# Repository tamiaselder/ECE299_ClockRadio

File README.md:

UVic ECE 299 term project repository, Clock radio

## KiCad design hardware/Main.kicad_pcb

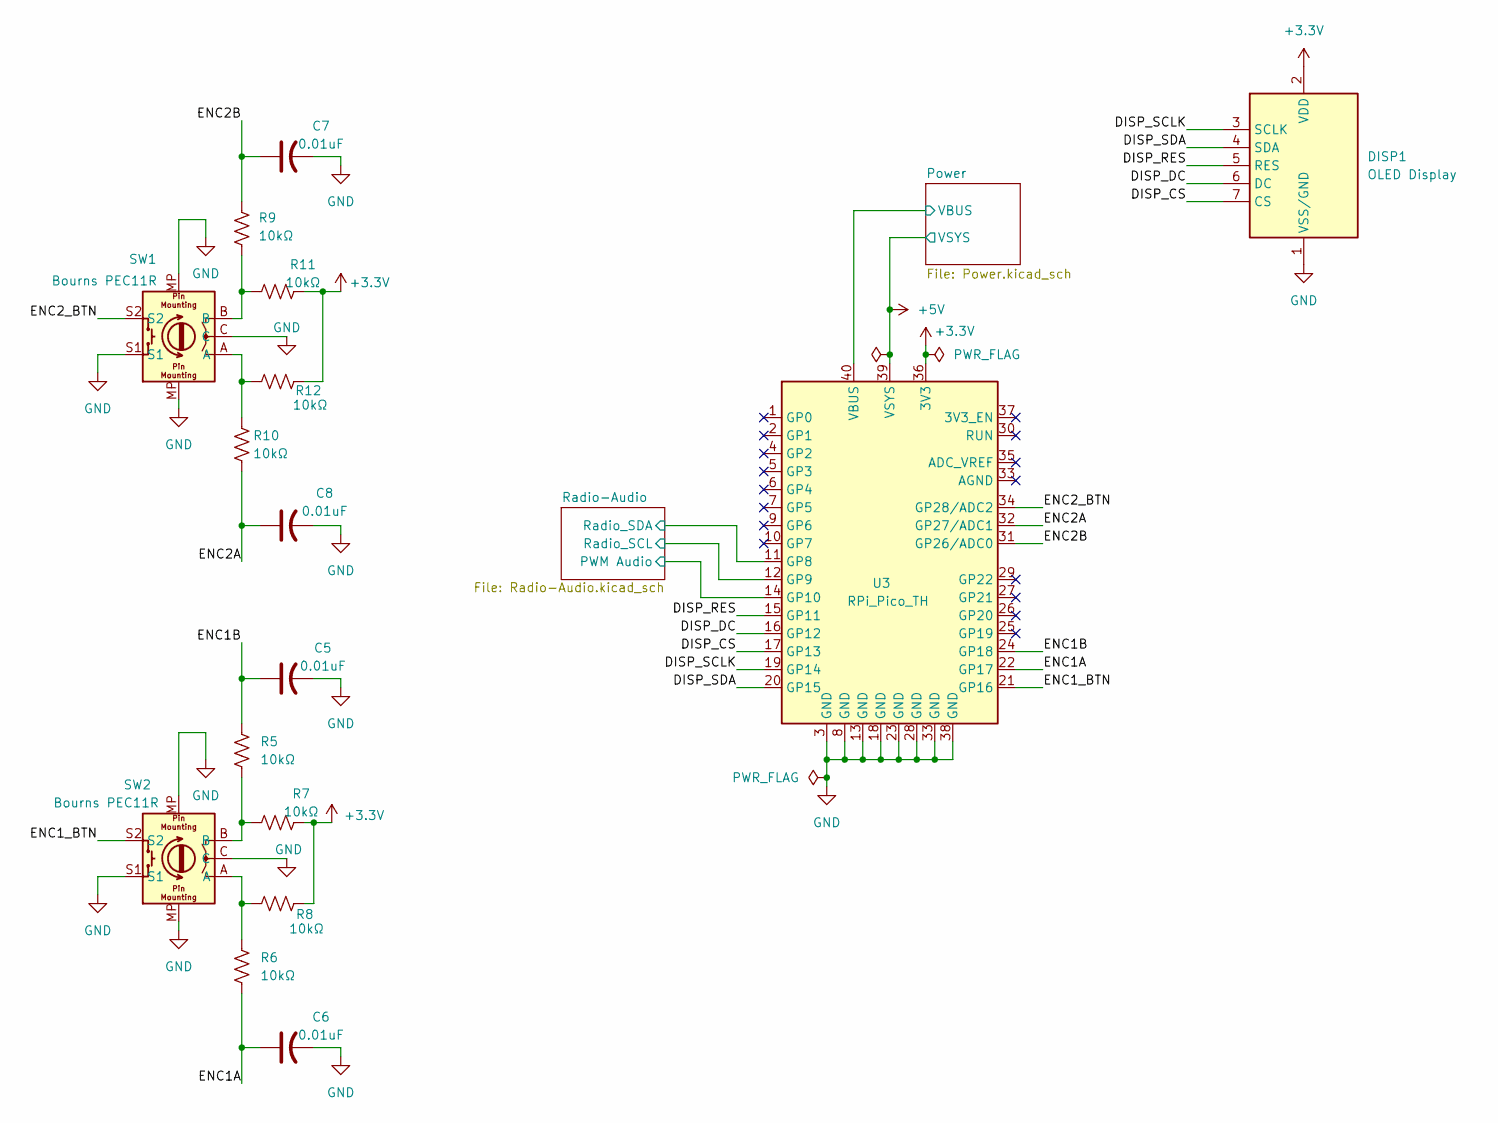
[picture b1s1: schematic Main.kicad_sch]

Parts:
C5, C6, C7, C8: 0.01uF; C_1206_3216Metric
DISP1: OLED Display; PinHeader_1x07_P2.00mm_Vertical
R5, R6, R7, R8, R9, R10, R11, R12: 10kΩ; R_1206_3216Metric
SW1, SW2: Bourns PEC11R; RotaryEncoder_Alps_EC12E-Switch_Vertical_H20mm
U3: RPi_Pico_TH

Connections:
+3.3V: DISP1.2 (VDD), R7.2, R8.2, R11.2, R12.2, U3.36 (3V3); also elsewhere on the board
+5V: U3.39 (VSYS); also elsewhere on the board
/DISP_CS: DISP1.7 (CS), U3.17 (GP13)
/DISP_DC: DISP1.6 (DC), U3.16 (GP12)
/DISP_RES: DISP1.5 (RES), U3.15 (GP11)
/DISP_SCLK: DISP1.3 (SCLK), U3.19 (GP14)
/DISP_SDA: DISP1.4 (SDA), U3.20 (GP15)
/ENC1A: C6.1, R6.1, U3.22 (GP17)
/ENC1B: C5.1, R5.2, U3.24 (GP18)
/ENC1_BTN: SW2.S2, U3.21 (GP16)
/ENC2A: C8.1, R10.1, U3.32 (GP27/ADC1)
/ENC2B: C7.1, R9.2, U3.31 (GP26/ADC0)
/ENC2_BTN: SW1.S2, U3.34 (GP28/ADC2)
/Power/VBUS: U3.40 (VBUS); also elsewhere on the board
/Radio-Audio/PWM Audio: U3.14 (GP10); also elsewhere on the board
/Radio-Audio/Radio_SCL: U3.12 (GP9); also elsewhere on the board
/Radio-Audio/Radio_SDA: U3.11 (GP8); also elsewhere on the board
GND: C5.2, C6.2, C7.2, C8.2, DISP1.1 (VSS/GND), SW1.C, SW1.MP, SW1.S1, SW2.C, SW2.MP, SW2.S1, U3.3 (GND), U3.8 (GND), U3.13 (GND), U3.18 (GND), U3.23 (GND), U3.28 (GND), U3.33 (GND), U3.38 (GND); also elsewhere on the board
unnamed: R5.1, R7.1, SW2.B
unnamed: R6.2, R8.1, SW2.A
unnamed: R10.2, R12.1, SW1.A
unnamed: R9.1, R11.1, SW1.B

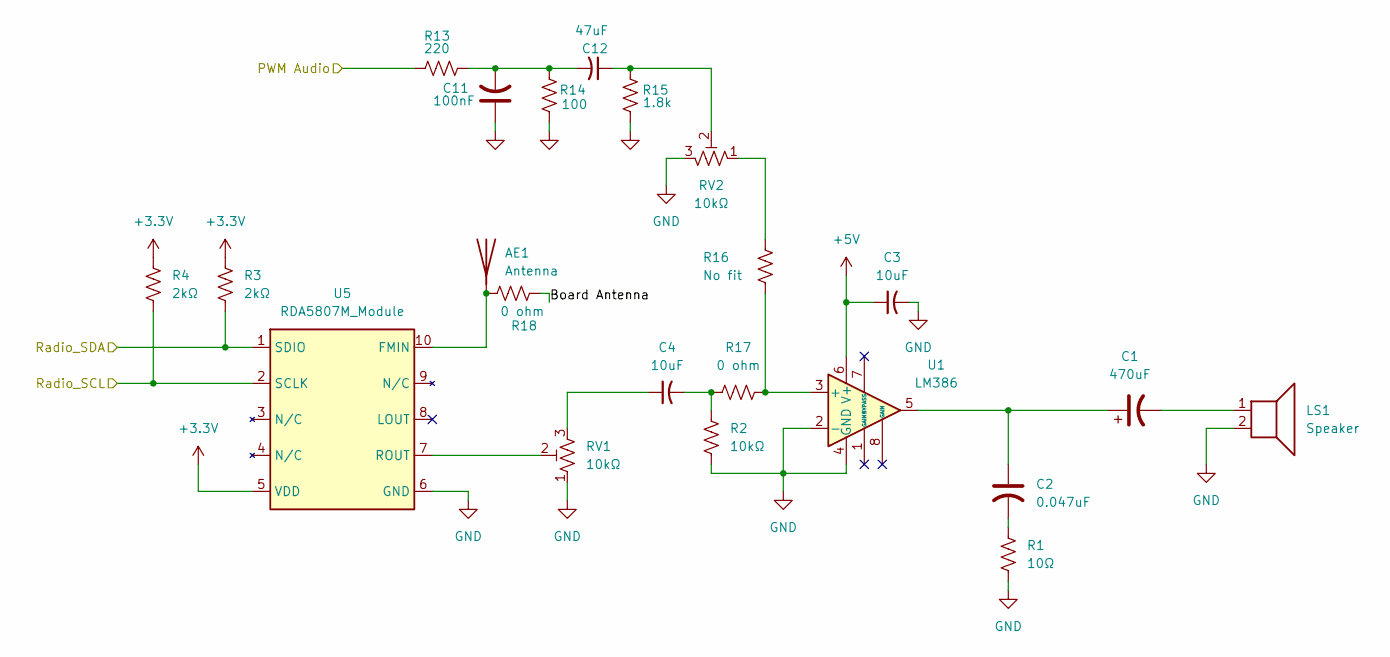
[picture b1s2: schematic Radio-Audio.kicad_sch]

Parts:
AE1: Antenna; PinHeader_1x01_P2.00mm_Vertical
C1: 470uF; CP_EIA-7343-30_AVX-N
C2: 0.047uF; C_1206_3216Metric
C3, C4: 10uF; C_1206_3216Metric
C11: 100nF; C_1206_3216Metric
C12: 47uF; C_1206_3216Metric
LS1: Speaker; TerminalBlock_MaiXu_MX126-5.0-02P_1x02_P5.00mm
R1: 10Ω; R_1206_3216Metric
R2: 10kΩ; R_1206_3216Metric
R3, R4: 2kΩ; R_1206_3216Metric
R13: 220; R_1206_3216Metric
R14: 100; R_1206_3216Metric
R15: 1.8k; R_1206_3216Metric
R16: No fit; R_1206_3216Metric
R17, R18: 0 ohm; R_1206_3216Metric
RV1, RV2: 10kΩ; Potentiometer_Bourns_3314J_Vertical
U1: LM386; DIP-8_W7.62mm_Socket
U5: RDA5807M_Module; RDA5807M_Module_SM

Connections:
+3.3V: R3.2, R4.1, U5.5 (VDD); also elsewhere on the board
+5V: C3.1, U1.6 (V+); also elsewhere on the board
/Radio-Audio/Board Antenna: R18.2
/Radio-Audio/PWM Audio: R13.2; also elsewhere on the board
/Radio-Audio/Radio_SCL: R4.2, U5.2 (SCLK); also elsewhere on the board
/Radio-Audio/Radio_SDA: R3.1, U5.1 (SDIO); also elsewhere on the board
GND: C3.2, C11.1, LS1.2, R1.2, R2.2, R14.1, R15.1, RV1.1, RV2.3, U1.2 (-), U1.4 (GND), U5.6 (GND); also elsewhere on the board
unnamed: AE1.1 (A), R18.1, U5.10 (FMIN)
unnamed: C1.1, C2.1, U1.5
unnamed: C1.2, LS1.1
unnamed: C2.2, R1.1
unnamed: C4.1, RV1.3
unnamed: C4.2, R2.1, R17.1
unnamed: C11.2, C12.2, R13.1, R14.2
unnamed: C12.1, R15.2, RV2.2
unnamed: R16.1, RV2.1
unnamed: R16.2, R17.2, U1.3 (+)
unnamed: RV1.2, U5.7 (ROUT)

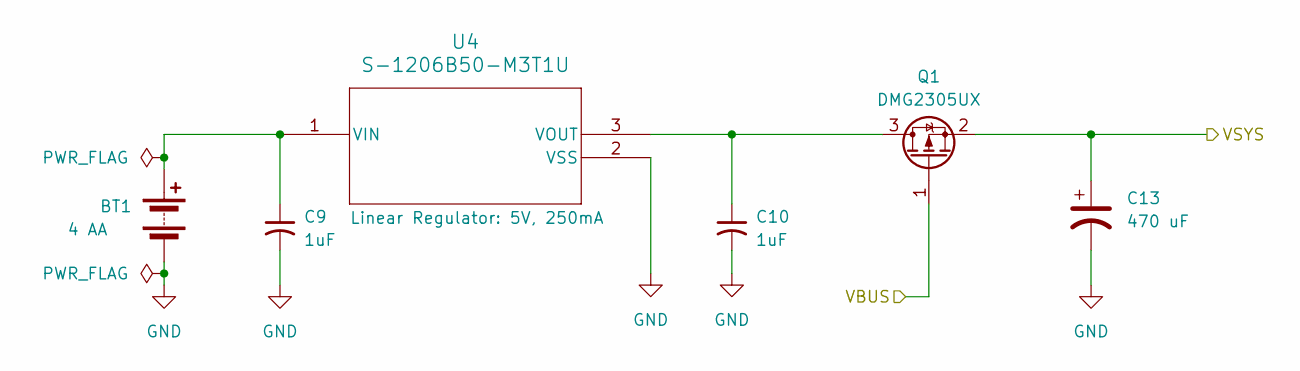
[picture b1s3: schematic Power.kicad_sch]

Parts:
BT1: 4 AA; TerminalBlock_MaiXu_MX126-5.0-02P_1x02_P5.00mm
C9, C10: 1uF; C_1206_3216Metric
C13: 470 uF; CP_EIA-7343-30_AVX-N
Q1: DMG2305UX; SOT-23
U4: S-1206B50-M3T1U; SOT-23-3

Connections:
+5V: C13.1, Q1.2 (S); also elsewhere on the board
/Power/VBUS: Q1.1 (G); also elsewhere on the board
GND: BT1.2 (-), C9.2, C10.2, C13.2, U4.2 (VSS); also elsewhere on the board
unnamed: BT1.1 (+), C9.1, U4.1 (VIN)
unnamed: C10.1, Q1.3 (D), U4.3 (VOUT)

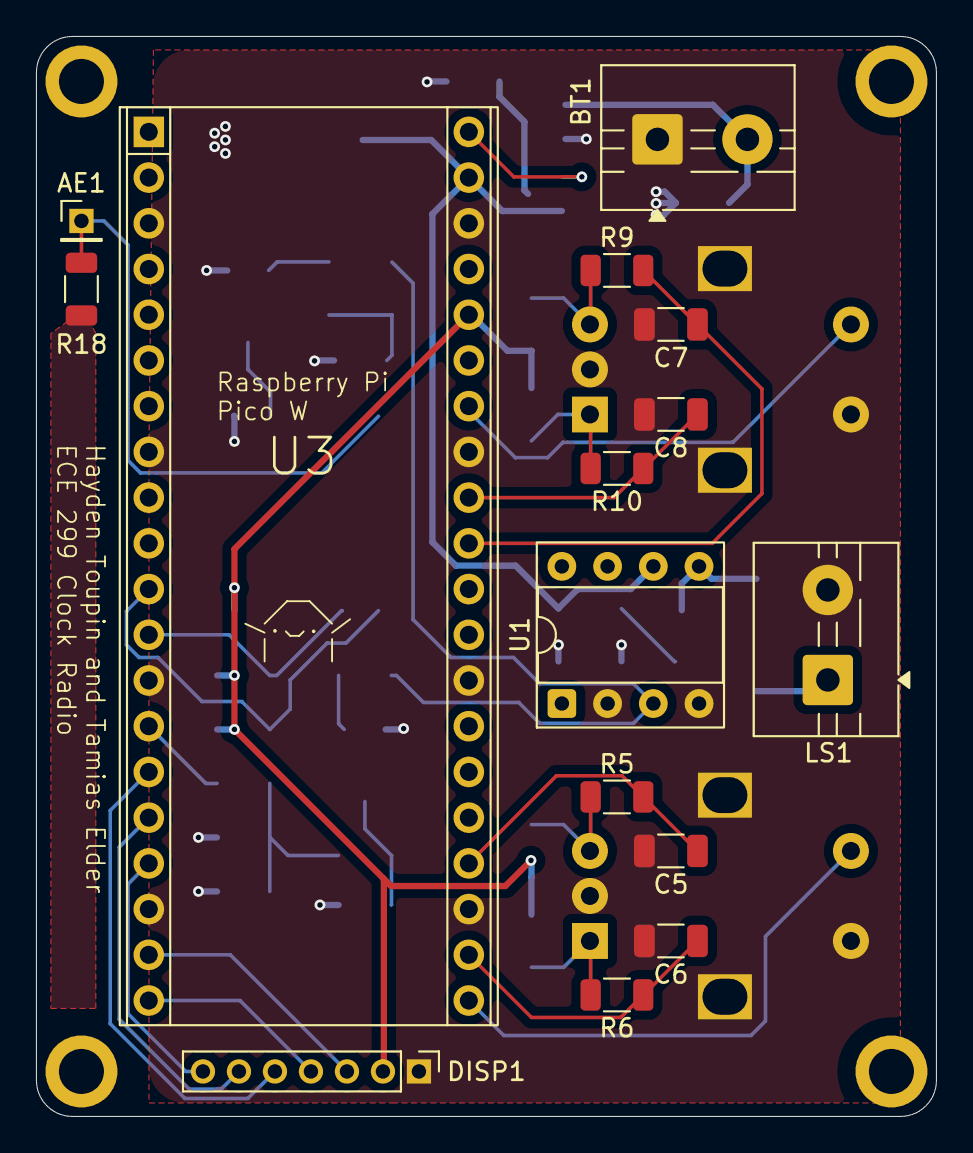
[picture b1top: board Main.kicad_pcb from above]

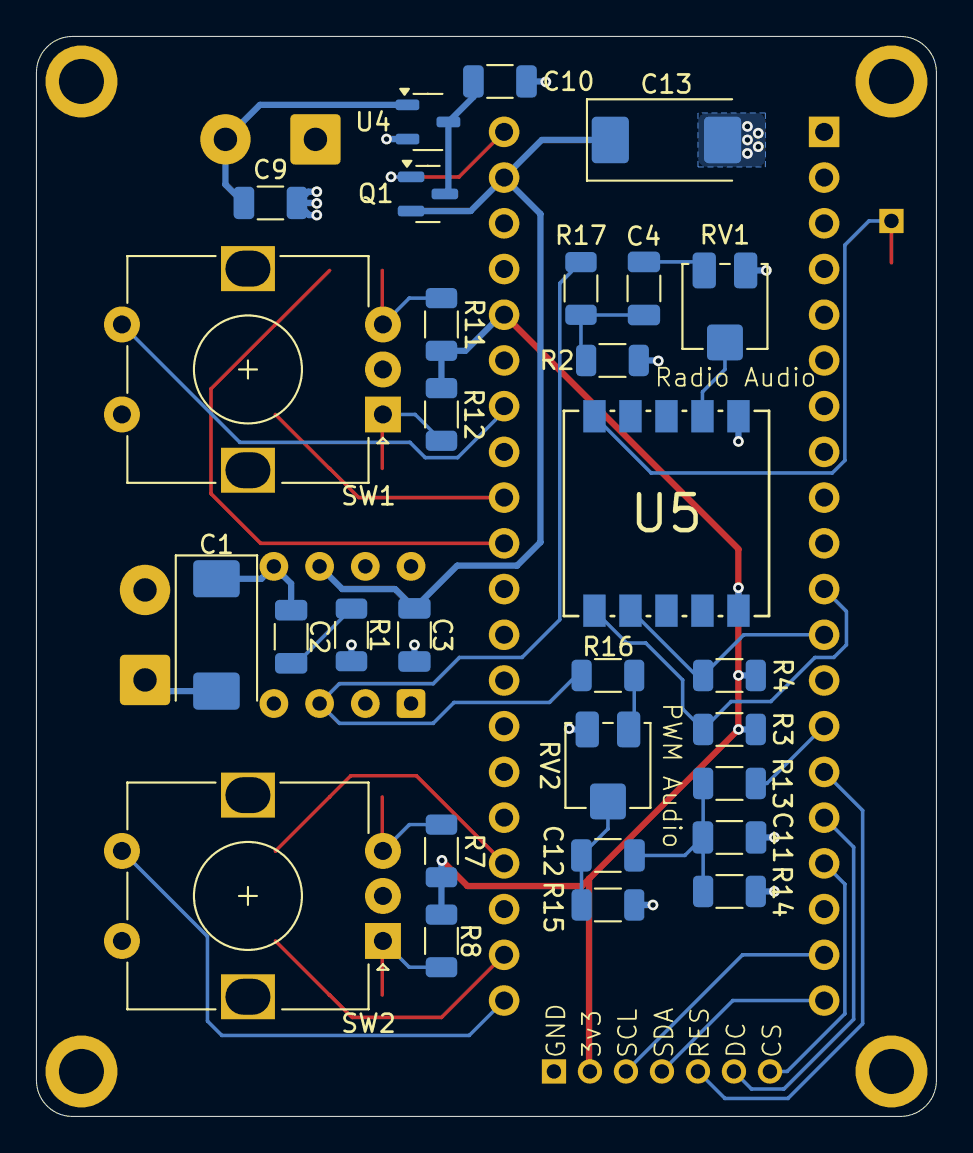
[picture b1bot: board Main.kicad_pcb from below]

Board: 2 copper layers, 50.0 x 60.0 mm, 44 parts (29 on the bottom side), 35 nets.

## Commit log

2025-06-12 cleaned
2025-06-12 Adding Provided Drivers
2025-06-12 ignoed local settings
2025-06-12 Adding Kicad Project
2025-06-12 sorting project files
2025-06-12 test commit
2025-06-12 test kicad
2025-06-12 organize
2025-06-13 started doing stuff (barely)
2025-06-13 radio testing
2025-06-17 Rotary encoder code
2025-06-18 Rotary Encoder Code + Audio Circuit
2025-06-18 Added Radio Module to circuit
2025-06-19 Updated Encoder Circuit/Code
2025-06-20 Assigned Pinout to Subsystems
2025-06-20 Powerchain
    Powerchain first draft done
2025-06-20 Added Button circuit
2025-06-21 Rough Board Layout
2025-06-21 Revised PCB Layout
2025-06-22 Reduced Component Sizes + Added Mounting Holes
2025-06-22 PWM Audio, Power fix
2025-06-24 Repositioned + Added volume potentiometer to PMW Audio
2025-06-24 Did it all lmao (pcb traces ready for full review)
2025-06-24 done for real this time
2025-06-24 PCB tweaks
2025-06-26 pcb tweaks after TA tips
2025-06-27 Minor Changes
2025-06-28 Changed mounting hole radius to 2.5mm
2025-07-17 Pin changes
2025-07-18 Fixed display Driver
2025-07-23 Rotary Class
2025-07-23 Added software flow chart.drawio
2025-07-23 Added Untitled Diagram.drawio
2025-07-24 display stuff hehe
2025-07-26 framebuf2
2025-07-26 display classes
2025-07-26 Added to Menu
2025-07-26 Main code
2025-07-26 Added Radio Functionality to Menu
2025-07-27 settings stuff
2025-07-27 started display stuff
2025-07-27 screen blocking.drawio
2025-07-28 standby and time menu screens done
2025-07-28 Fixed encoder and menu
2025-07-28 Screens done
2025-07-29 Fixed screens + added some alarm functionality to menu
2025-07-29 Added PWM Functionality
2025-07-29 Current Things on Pico
2025-07-30 fixed? fm_radio
2025-07-30 Alarm screen
2025-07-30 Meow
2025-07-30 Low quality meow
2025-07-30 build as of 11PM, july 29, 2025
2025-07-30 Stuff and Things
2025-07-30 More things
2025-07-30 updated audio and added clips and screen
2025-07-30 Implemented things in menu
2025-07-30 Fixed encoder class
2025-07-30 sample and screens updated and fixed
2025-07-30 fixed scerens again
2025-07-30 WEEZER
2025-07-30 FIxed Main and Menu
2025-07-30 It works!!
2025-07-30 updated weezer
2025-07-30 Again stuff and things
2025-07-30 snoozing state to the alarm menu display.
2025-07-30 Added Sound Files
2025-07-30 Added Faces
2025-07-30 organized source files into demo_build and previous_files directories
2025-07-30 Final Build for lab demonstration
